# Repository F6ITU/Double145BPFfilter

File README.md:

# Double145BPFfilter
Double 145MHz BPF filter. Retrofit for a better rejection

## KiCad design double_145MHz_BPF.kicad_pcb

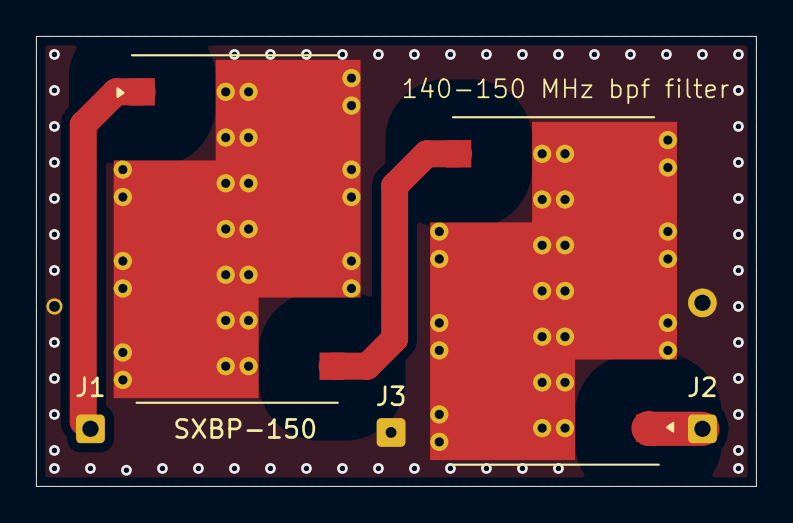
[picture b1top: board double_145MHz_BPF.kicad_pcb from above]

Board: 2 copper layers, 40.0 x 25.0 mm, 5 parts (0 on the bottom side), 4 nets.

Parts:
J1, J2: Conn_01x02_Socket; SolderWire-0.1sqmm_1x02_P3.6mm_D0.4mm_OD1mm
J3: Conn_01x01_Socket; SolderWire-0.1sqmm_1x01_D0.4mm_OD1mm
U1, U2: SXBP-140; Mini-Circuits_HF1139_LandPatternPL-230

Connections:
GND: J1.2, J2.2, J3.1, U1.2 (GND), U1.3 (GND), U1.4 (GND), U1.5 (GND), U1.6 (GND), U1.7 (GND), U2.2 (GND), U2.3 (GND), U2.4 (GND), U2.5 (GND), U2.6 (GND), U2.7 (GND)
unnamed: J1.1, U2.1 (IN)
unnamed: J2.1, U1.1 (IN)
unnamed: U1.8 (OUT), U2.8 (OUT)

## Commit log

2024-07-10 80 dB rejection double filter V1, initial commit
2024-07-11 new gerber files
2024-09-27 new gerber, vna analyze, test setup pictures
